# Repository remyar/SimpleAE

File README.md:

# SimpleAE
Simple electronic ignition for four stroke engine

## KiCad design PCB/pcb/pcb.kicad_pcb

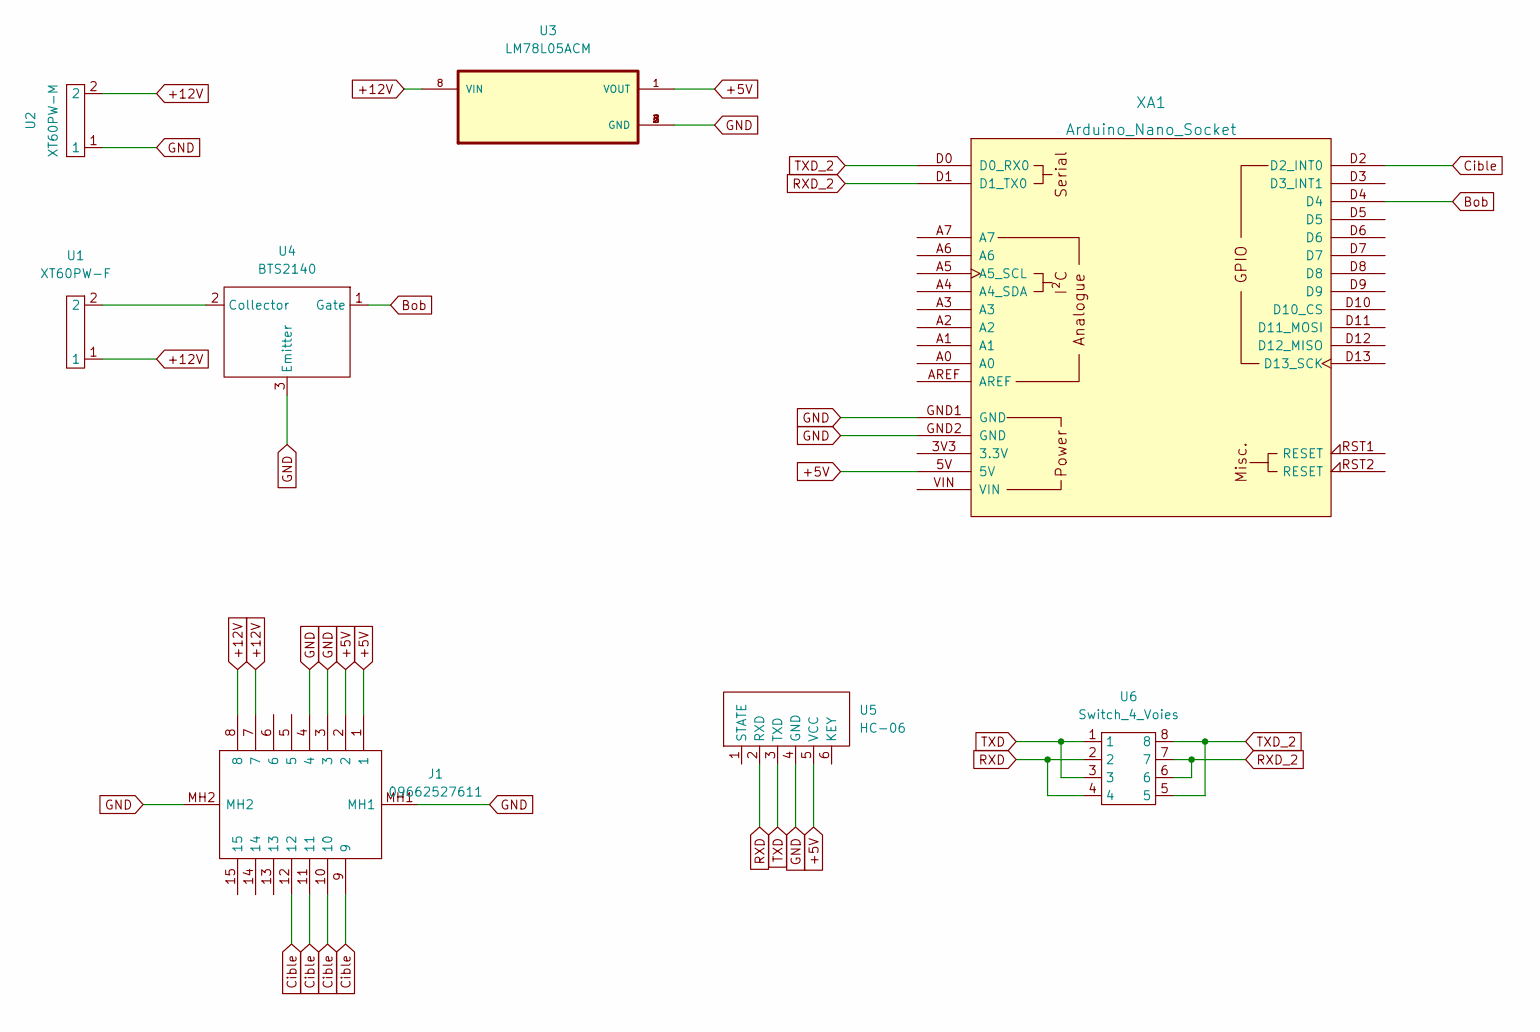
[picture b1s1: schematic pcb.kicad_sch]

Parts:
J1: 09662527611; Mouser Part Number 617-09-66-252-7611
U1: XT60PW-F
U2: XT60PW-M
U3: LM78L05ACM; SOIC127P599X175-8N
U4: BTS2140; TRANS_IPB027N10N3_G
U5: HC-06
U6: Switch_4_Voies; DIP-8_300_ELL
XA1: Arduino_Nano_Socket; arduino_nano

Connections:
+5V: J1.1, J1.2, U3.1 (VOUT), U5.5 (VCC), XA1.5V
+12V: J1.7, J1.8, U1.1, U2.2, U3.8 (VIN)
Bob: U4.1 (Gate), XA1.D4
Cible: J1.9, J1.10, J1.11, J1.12, XA1.D2 (D2_INT0)
GND: J1.3, J1.4, J1.MH1, J1.MH2, U2.1, U3.2 (GND), U3.3 (GND), U3.6 (GND), U3.7 (GND), U4.3 (Emitter), U5.4 (GND), XA1.GND1 (GND), XA1.GND2 (GND)
unnamed: U1.2, U4.2 (Collector)
RXD: U5.2 (RXD), U6.2, U6.4
RXD_2: U6.6, U6.7, XA1.D1 (D1_TX0)
TXD: U5.3 (TXD), U6.1, U6.3
TXD_2: U6.5, U6.8, XA1.D0 (D0_RX0)

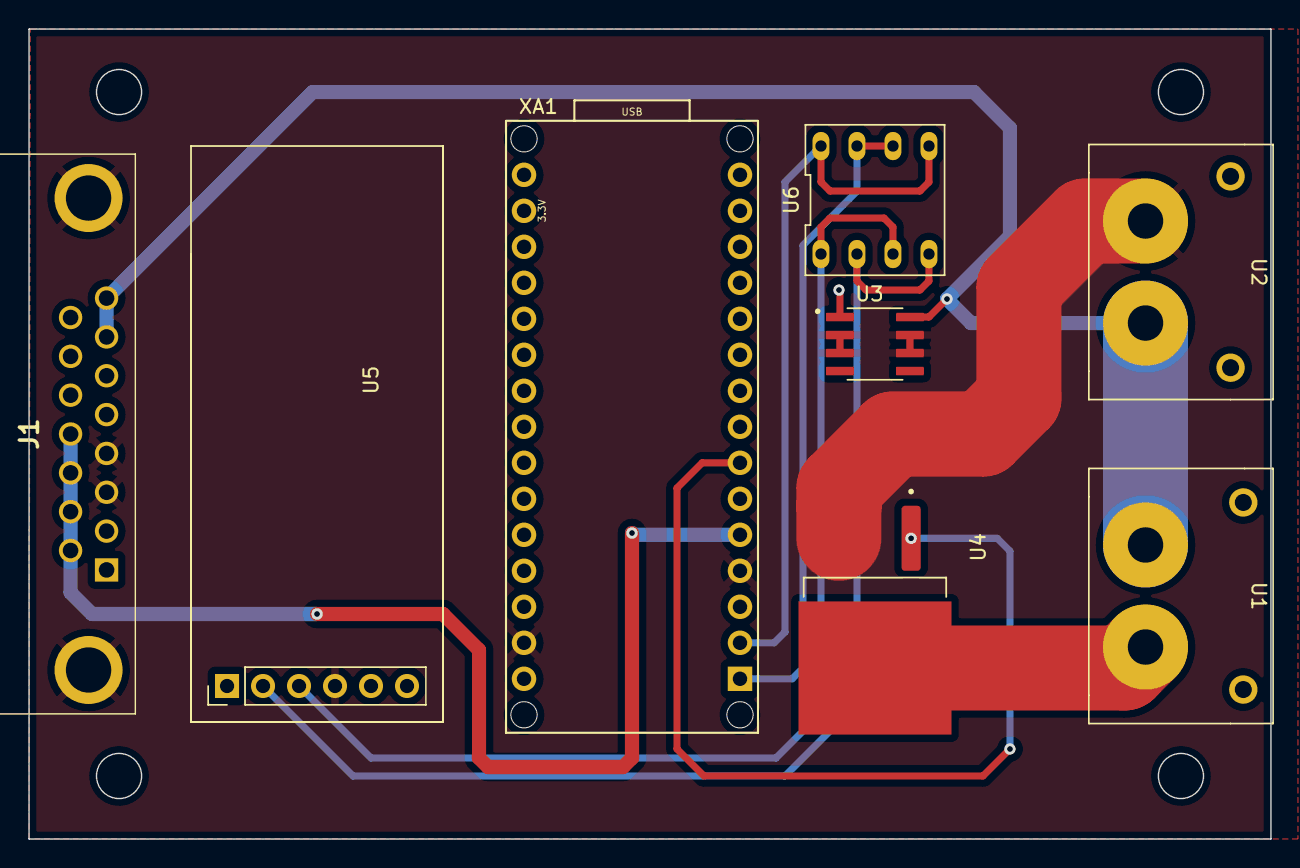
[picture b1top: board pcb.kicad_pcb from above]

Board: 2 copper layers, 87.6 x 57.1 mm, 8 parts (0 on the bottom side), 10 nets.

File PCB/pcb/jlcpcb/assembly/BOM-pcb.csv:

Comment,Designator,Footprint,LCSC
Switch_4_Voies,U6,DIP-8_300_ELL,
LM78L05ACM,U3,SOIC127P599X175-8N,
09662527611,J1,09662527611,
XT60PW-M,U2,XT60PW-M,
HC-06,U5,HC-06,
Arduino_Nano_Socket,XA1,arduino_nano,
XT60PW-F,U1,XT60PW-F,
BTS2140,U4,TRANS_IPB027N10N3_G,

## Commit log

2020-11-16 add soft arduino
2022-06-27 ouch
2022-07-07 add pcb
2022-07-14 add capteur
2022-10-31 addpcb
